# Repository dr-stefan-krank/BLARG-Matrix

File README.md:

**BLARG-Matrix is an open analog audio matrix board to be integrated in smart home applications.**

Its purpose is to build a central multi-room audio system.
For example 4 players connected to 8 rooms in stereo mode, 8 players to 16 rooms in mono configuration or anything in between.

**Features**

- 8x16 matrix chip to route any input to one or more outputs.
- All outputs are digitally volume controlled.
- 11 unused GPIO of the ESP
- A 16 GPIO IO expander allows for control of a 16 channel relais board for switching amplifiers.
- All inputs and outputs are unbalanced line level.

Note: The board has to be equipped with a standard ESP32-DEVKIT-C.

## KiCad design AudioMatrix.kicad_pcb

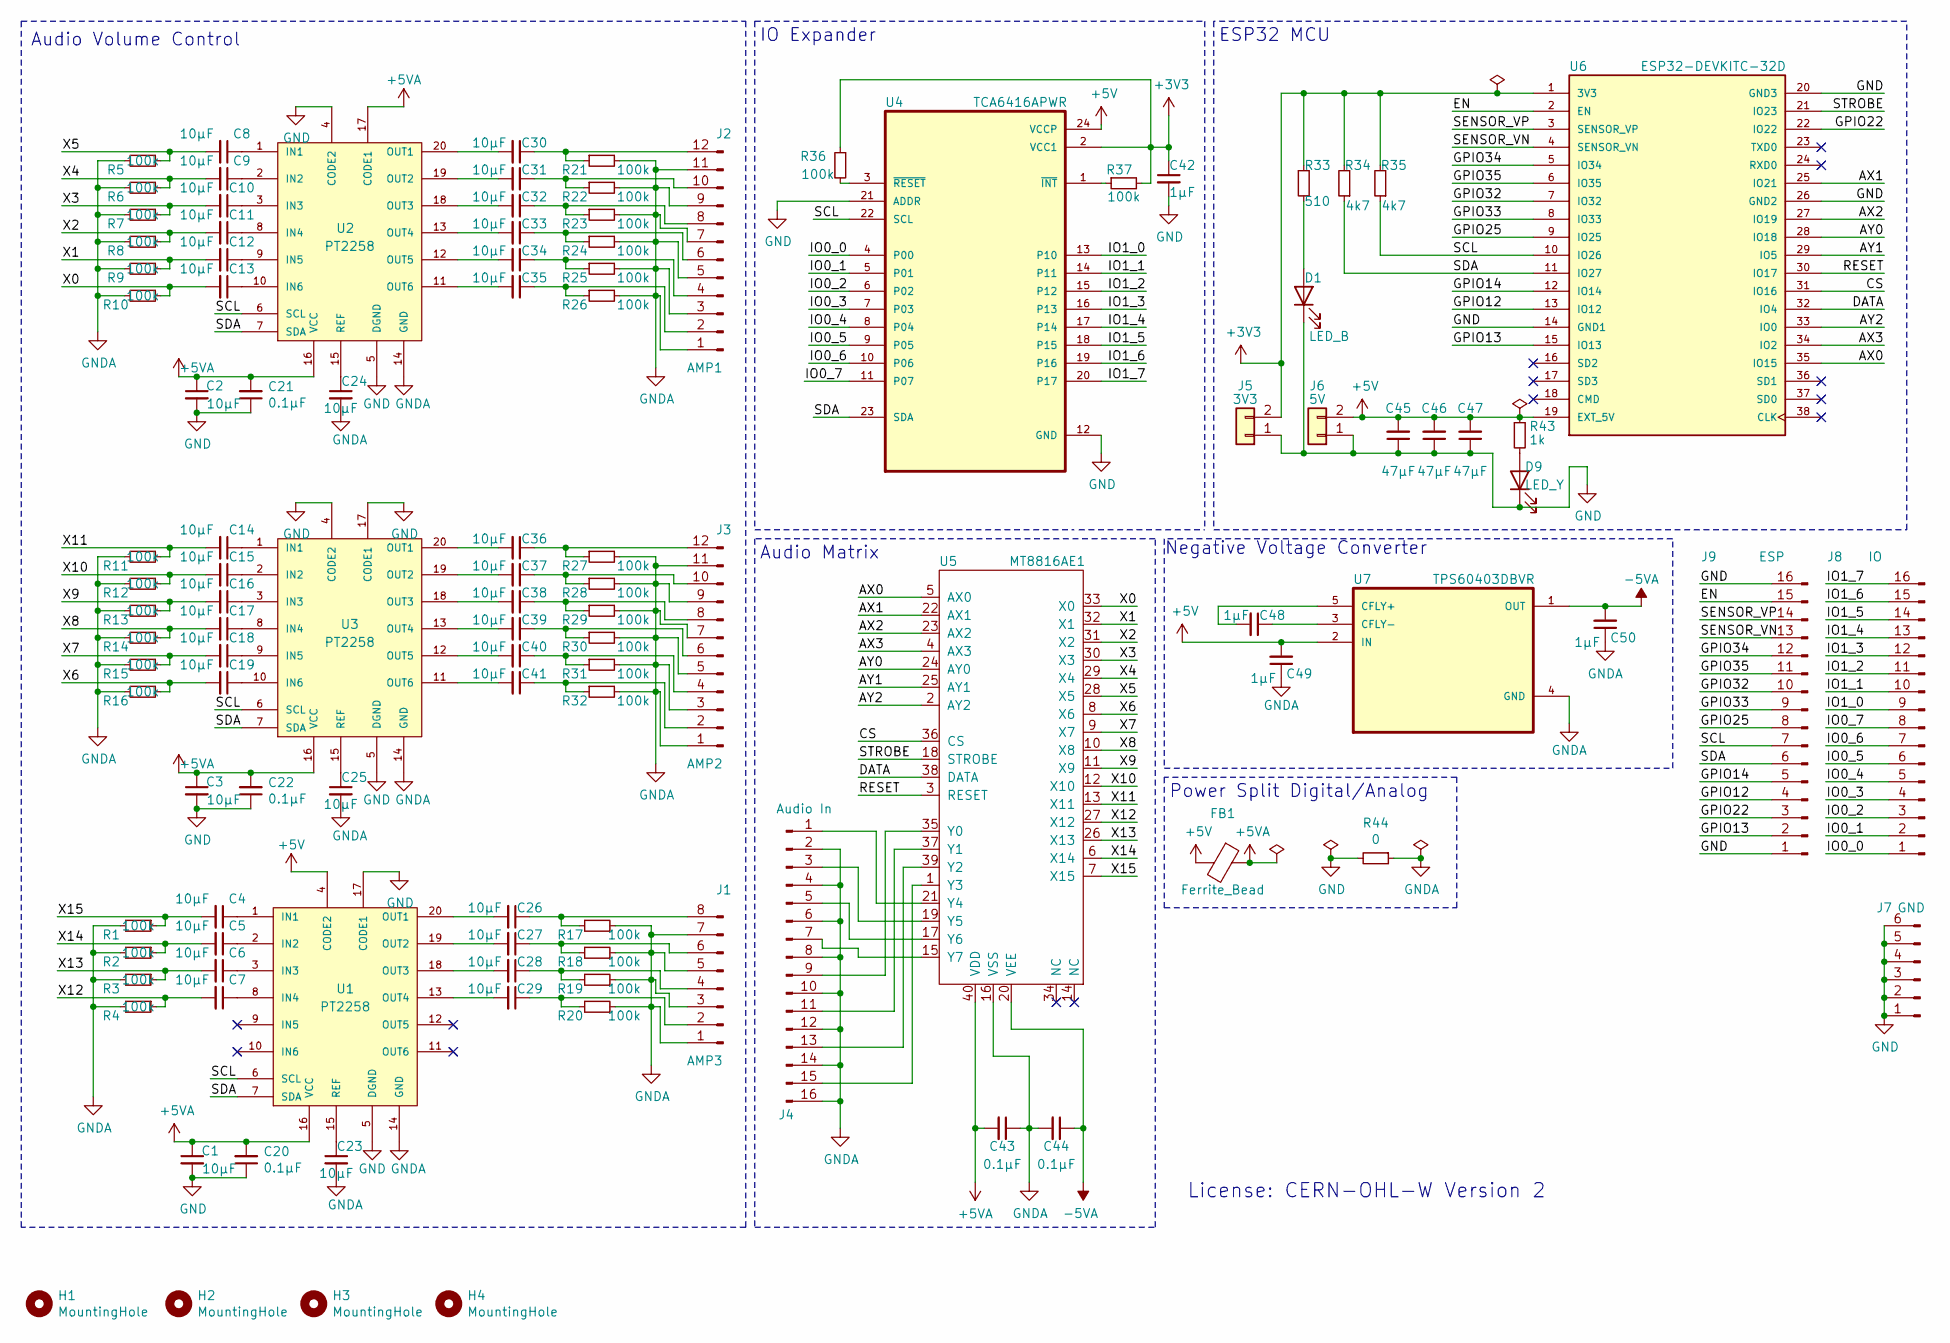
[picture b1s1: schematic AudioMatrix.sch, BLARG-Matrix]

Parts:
C1, C2, C3, C4, C5, C6, C7, C8, C9, C10, C11, C12, C13, C14, C15, C16, C17, C18, C19, C23, C24, C25, C26, C27, C28, C29, C31, C32, C33, C34, C35, C37, C38, C39, C40, C41: 10μF; C_0805_2012Metric
C20, C21, C22, C44: 0.1μF; C_0805_2012Metric
C30: 10μF; C_0805_2012Metric; LCSC C15850
C36: 10μF; C_0805_2012Metric; LCSC C1785
C42, C48, C49, C50: 1μF; C_0805_2012Metric; LCSC C28323
C43: 0.1μF; C_0805_2012Metric; LCSC C49678
C45, C46, C47: 47μF; C_1206_3216Metric; LCSC C96123
D1: LED_B; D_0603_1608Metric; LCSC C72041
D9: LED_Y; D_0603_1608Metric; LCSC C72038
FB1: Ferrite_Bead; L_1206_3216Metric; LCSC C94305
H1, H2, H3, H4: MountingHole; MountingHole_3.2mm_M3
J1: AMP3; PinHeader_1x08_P2.54mm_Vertical
J2: AMP1; PinHeader_1x12_P2.54mm_Vertical
J3: AMP2; PinHeader_1x12_P2.54mm_Vertical
J4: Audio In; PinHeader_1x16_P2.54mm_Vertical
J5: 3V3; PinHeader_1x02_P2.54mm_Vertical
J6: 5V; PinHeader_1x02_P2.54mm_Vertical
J7: GND; PinHeader_1x06_P2.54mm_Vertical
J8: IO; PinHeader_1x16_P2.54mm_Vertical
J9: ESP; PinHeader_1x16_P2.54mm_Vertical
R1, R2, R3, R4, R6, R7, R8, R9, R10, R11, R12, R13, R14, R15, R16, R17, R18, R19, R20, R21, R22, R23, R24, R25, R26, R27, R28, R29, R30, R31, R32, R36, R37: 100k; R_0603_1608Metric
R5: 100k; R_0603_1608Metric; LCSC C25803
R33: 510; R_0603_1608Metric; LCSC C23193
R34, R35: 4k7; R_0603_1608Metric; LCSC C23162
R43: 1k; R_0603_1608Metric; LCSC C21190
R44: 0; R_0805_2012Metric; LCSC C17477
U1, U2, U3: PT2258; SOIC-20W_7.5x12.8mm_P1.27mm; LCSC C99213
U4: TCA6416APWR; SOP65P640X120-24N; LCSC C130203
U5: MT8816AE1; DIP-40_W15.24mm_Socket
U6: ESP32-DEVKITC-32D; MODULE_ESP32-DEVKITC-32D; PARTREV 4
U7: TPS60403DBVR; SOT95P280X145-5N; LCSC C11338

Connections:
+3V3: C42.1, J5.2, R33.1, R34.2, R35.2, R36.1, R37.2, U4.2 (VCC1), U6.1 (3V3)
+5V: C45.2, C46.2, C47.2, C49.2, FB1.2, J6.2, R43.1, U1.4 (CODE2), U4.24 (VCCP), U6.19 (EXT_5V), U7.2 (IN)
+5VA: C1.1, C2.1, C3.1, C20.2, C21.2, C22.2, C43.2, FB1.1, U1.16 (VCC), U2.16 (VCC), U2.17 (CODE1), U3.16 (VCC), U5.40 (VDD)
-5VA: C44.1, C50.2, U5.20 (VEE), U7.1 (OUT)
/AX0: U5.5 (AX0), U6.35 (IO15)
/AX1: U5.22 (AX1), U6.25 (IO21)
/AX2: U5.23 (AX2), U6.27 (IO19)
/AX3: U5.4 (AX3), U6.34 (IO2)
/AY0: U5.24 (AY0), U6.28 (IO18)
/AY1: U5.25 (AY1), U6.29 (IO5)
/AY2: U5.2 (AY2), U6.33 (IO0)
/CS: U5.36 (CS), U6.31 (IO16)
/DATA: U5.38 (DATA), U6.32 (IO4)
/EN: J9.15, U6.2 (EN)
/GPIO12: J9.4, U6.13 (IO12)
/GPIO13: J9.2, U6.15 (IO13)
/GPIO14: J9.5, U6.12 (IO14)
/GPIO22: J9.3, U6.22 (IO22)
/GPIO25: J9.8, U6.9 (IO25)
/GPIO32: J9.10, U6.7 (IO32)
/GPIO33: J9.9, U6.8 (IO33)
/GPIO34: J9.12, U6.5 (IO34)
/GPIO35: J9.11, U6.6 (IO35)
/IO0_0: J8.1, U4.4 (P00)
/IO0_1: J8.2, U4.5 (P01)
/IO0_2: J8.3, U4.6 (P02)
/IO0_3: J8.4, U4.7 (P03)
/IO0_4: J8.5, U4.8 (P04)
/IO0_5: J8.6, U4.9 (P05)
/IO0_6: J8.7, U4.10 (P06)
/IO0_7: J8.8, U4.11 (P07)
/IO1_0: J8.9, U4.13 (P10)
/IO1_1: J8.10, U4.14 (P11)
/IO1_2: J8.11, U4.15 (P12)
/IO1_3: J8.12, U4.16 (P13)
/IO1_4: J8.13, U4.17 (P14)
/IO1_5: J8.14, U4.18 (P15)
/IO1_6: J8.15, U4.19 (P16)
/IO1_7: J8.16, U4.20 (P17)
/RESET: U5.3 (RESET), U6.30 (IO17)
/SCL: J9.7, R35.1, U1.6 (SCL), U2.6 (SCL), U3.6 (SCL), U4.22 (SCL), U6.10 (IO26)
/SDA: J9.6, R34.1, U1.7 (SDA), U2.7 (SDA), U3.7 (SDA), U4.23 (SDA), U6.11 (IO27)
/SENSOR_VN: J9.13, U6.4 (SENSOR_VN)
/SENSOR_VP: J9.14, U6.3 (SENSOR_VP)
/STROBE: U5.18 (STROBE), U6.21 (IO23)
/X0: C13.2, R10.1, U5.33 (X0)
/X1: C12.2, R9.1, U5.32 (X1)
/X2: C11.2, R8.1, U5.31 (X2)
/X3: C10.2, R7.1, U5.30 (X3)
/X4: C9.2, R6.1, U5.29 (X4)
/X5: C8.2, R5.1, U5.28 (X5)
/X6: C19.2, R16.1, U5.8 (X6)
/X7: C18.2, R15.1, U5.9 (X7)
/X8: C17.2, R14.1, U5.10 (X8)
/X9: C16.2, R13.1, U5.11 (X9)
/X10: C15.2, R12.1, U5.12 (X10)
/X11: C14.2, R11.1, U5.13 (X11)
/X12: C7.2, R4.1, U5.27 (X12)
/X13: C6.2, R3.1, U5.26 (X13)
/X14: C5.2, R2.1, U5.6 (X14)
/X15: C4.2, R1.1, U5.7 (X15)
GND: C1.2, C2.2, C3.2, C20.1, C21.1, C22.1, C42.2, C45.1, C46.1, C47.1, D1.1 (K), D9.1 (K), J5.1, J6.1, J7.1, J7.2, J7.3, J7.4, J7.5, J7.6, J9.1, J9.16, R44.2, U1.5 (DGND), U1.17 (CODE1), U2.4 (CODE2), U2.5 (DGND), U3.4 (CODE2), U3.5 (DGND), U3.17 (CODE1), U4.12 (GND), U4.21 (ADDR), U6.14 (GND1), U6.20 (GND3), U6.26 (GND2)
GNDA: C23.2, C24.2, C25.2, C43.1, C44.2, C49.1, C50.1, J1.1, J1.3, J1.5, J1.7, J2.1, J2.3, J2.5, J2.7, J2.9, J2.11, J3.1, J3.3, J3.5, J3.7, J3.9, J3.11, J4.2, J4.4, J4.6, J4.8, J4.10, J4.12, J4.14, J4.16, R1.2, R2.2, R3.2, R4.2, R5.2, R6.2, R7.2, R8.2, R9.2, R10.2, R11.2, R12.2, R13.2, R14.2, R15.2, R16.2, R17.2, R18.2, R19.2, R20.2, R21.2, R22.2, R23.2, R24.2, R25.2, R26.2, R27.2, R28.2, R29.2, R30.2, R31.2, R32.2, R44.1, U1.14 (GND), U2.14 (GND), U3.14 (GND), U5.16 (VSS), U7.4 (GND)
unnamed: C4.1, U1.1 (IN1)
unnamed: C5.1, U1.2 (IN2)
unnamed: C6.1, U1.3 (IN3)
unnamed: C7.1, U1.8 (IN4)
unnamed: C8.1, U2.1 (IN1)
unnamed: C9.1, U2.2 (IN2)
unnamed: C10.1, U2.3 (IN3)
unnamed: C11.1, U2.8 (IN4)
unnamed: C12.1, U2.9 (IN5)
unnamed: C13.1, U2.10 (IN6)
unnamed: C14.1, U3.1 (IN1)
unnamed: C15.1, U3.2 (IN2)
unnamed: C16.1, U3.3 (IN3)
unnamed: C17.1, U3.8 (IN4)
unnamed: C18.1, U3.9 (IN5)
unnamed: C19.1, U3.10 (IN6)
unnamed: C23.1, U1.15 (REF)
unnamed: C24.1, U2.15 (REF)
unnamed: C25.1, U3.15 (REF)
unnamed: C26.1, J1.8, R17.1
unnamed: C26.2, U1.20 (OUT1)
unnamed: C27.1, J1.6, R18.1
unnamed: C27.2, U1.19 (OUT2)
unnamed: C28.1, J1.4, R19.1
unnamed: C28.2, U1.18 (OUT3)
unnamed: C29.1, J1.2, R20.1
unnamed: C29.2, U1.13 (OUT4)
unnamed: C30.1, J2.12, R21.1
unnamed: C30.2, U2.20 (OUT1)
unnamed: C31.1, J2.10, R22.1
unnamed: C31.2, U2.19 (OUT2)
unnamed: C32.1, J2.8, R23.1
unnamed: C32.2, U2.18 (OUT3)
unnamed: C33.1, J2.6, R24.1
unnamed: C33.2, U2.13 (OUT4)
unnamed: C34.1, J2.4, R25.1
unnamed: C34.2, U2.12 (OUT5)
unnamed: C35.1, J2.2, R26.1
unnamed: C35.2, U2.11 (OUT6)
unnamed: C36.1, J3.12, R27.1
unnamed: C36.2, U3.20 (OUT1)
unnamed: C37.1, J3.10, R28.1
unnamed: C37.2, U3.19 (OUT2)
unnamed: C38.1, J3.8, R29.1
unnamed: C38.2, U3.18 (OUT3)
unnamed: C39.1, J3.6, R30.1
unnamed: C39.2, U3.13 (OUT4)
unnamed: C40.1, J3.4, R31.1
unnamed: C40.2, U3.12 (OUT5)
unnamed: C41.1, J3.2, R32.1
unnamed: C41.2, U3.11 (OUT6)
unnamed: C48.1, U7.3 (CFLY-)
unnamed: C48.2, U7.5 (CFLY+)
unnamed: D1.2 (A), R33.2
unnamed: D9.2 (A), R43.2
unnamed: J4.1, U5.21 (Y4)
unnamed: J4.3, U5.19 (Y5)
unnamed: J4.5, U5.17 (Y6)
unnamed: J4.7, U5.15 (Y7)
unnamed: J4.9, U5.35 (Y0)
unnamed: J4.11, U5.37 (Y1)
unnamed: J4.13, U5.39 (Y2)
unnamed: J4.15, U5.1 (Y3)
unnamed: R36.2, U4.3 (~RESET)
unnamed: R37.1, U4.1 (~INT)

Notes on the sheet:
Power Split Digital/Analog
Audio Matrix
IO Expander
ESP32 MCU
Audio Volume Control
Negative Voltage Converter
License: CERN-OHL-W Version 2

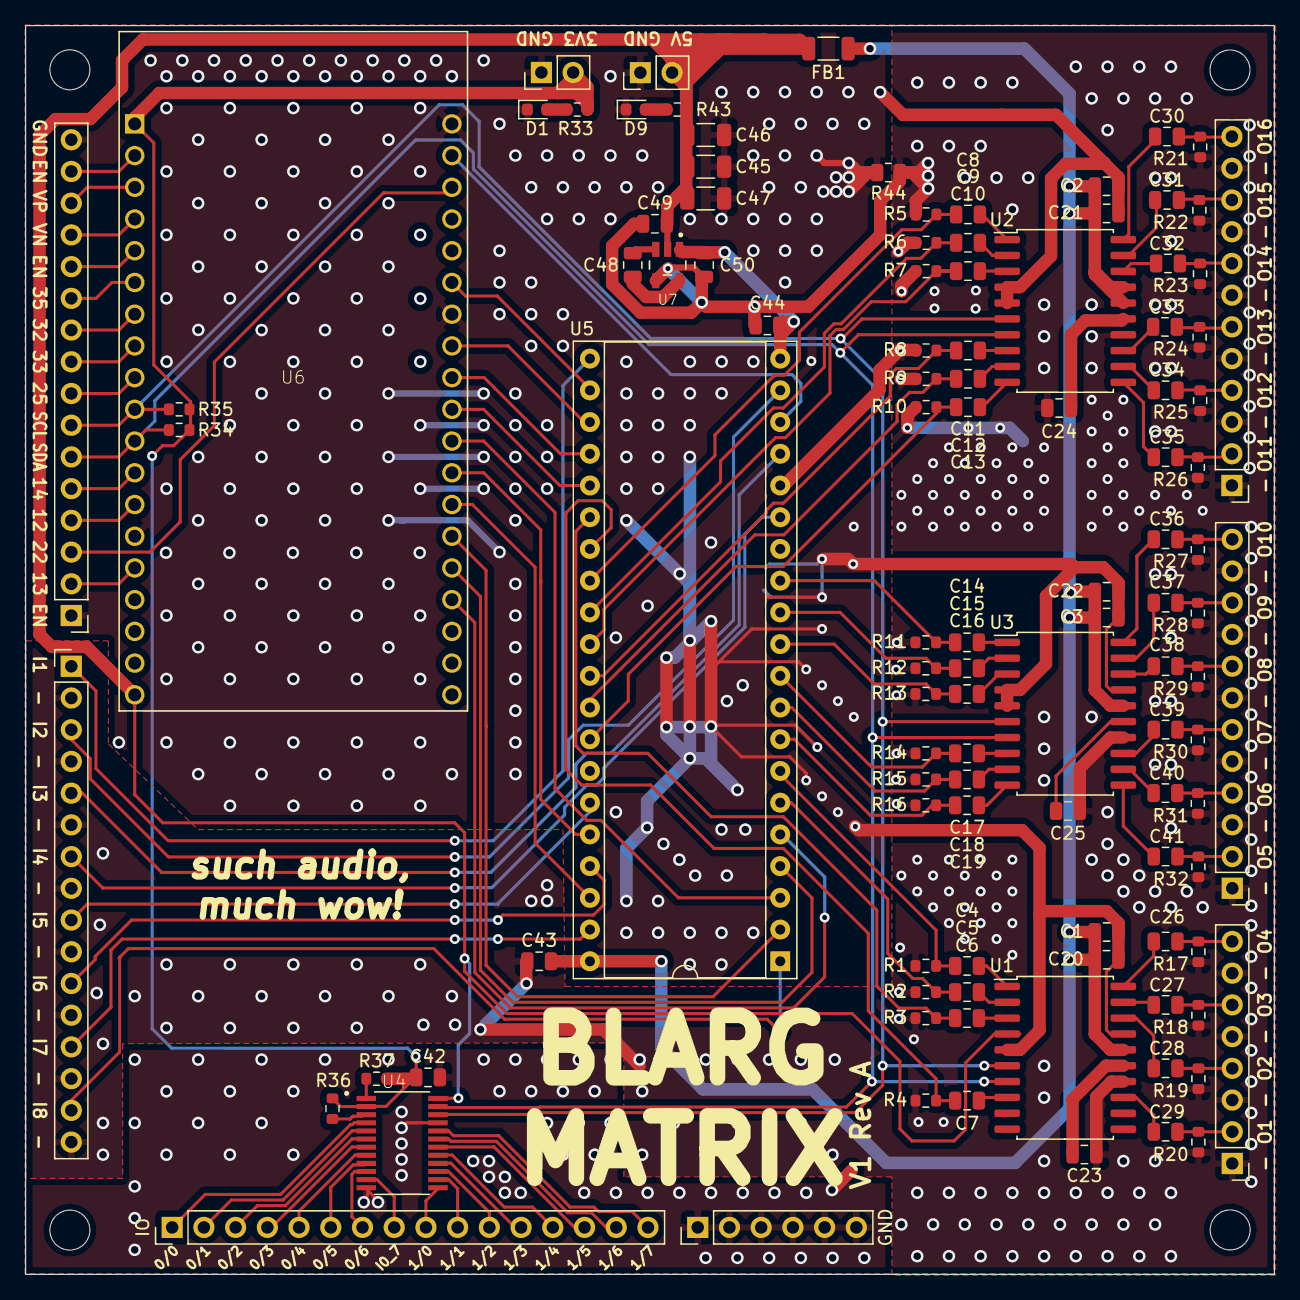
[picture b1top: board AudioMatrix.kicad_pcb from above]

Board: 2 copper layers, 100.0 x 100.0 mm, 112 parts (0 on the bottom side), 128 nets.

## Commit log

2021-03-06 First version
    no reviews yet
2021-03-06 Removed LEDs
2021-03-06 README Update
2021-03-06 Missing libraries.
2021-03-06 Replaced IO expander
2021-03-06 Fixed output cap design
2021-03-06 pcb cosmetics
    Step file for IO expander
2021-03-07 Changed component placement of volume controllers
2021-03-07 Net labeling and cleanup
2021-03-07 Git Ignore for fabrication outputs
2021-03-24 cosmetics
